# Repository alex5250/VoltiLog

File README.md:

# What it is 
VoltLogV2
This is an small device that allow record an voltage and current in two modes. The simplest mode is when the device is connected to PC and it sends data throught UART over USB. The second mode is when device is connected to power supply and just records data in internal memory. The all software and hardware is open sources and avabile there.
Is Kicad Export of PCB look:

Real PCB look:

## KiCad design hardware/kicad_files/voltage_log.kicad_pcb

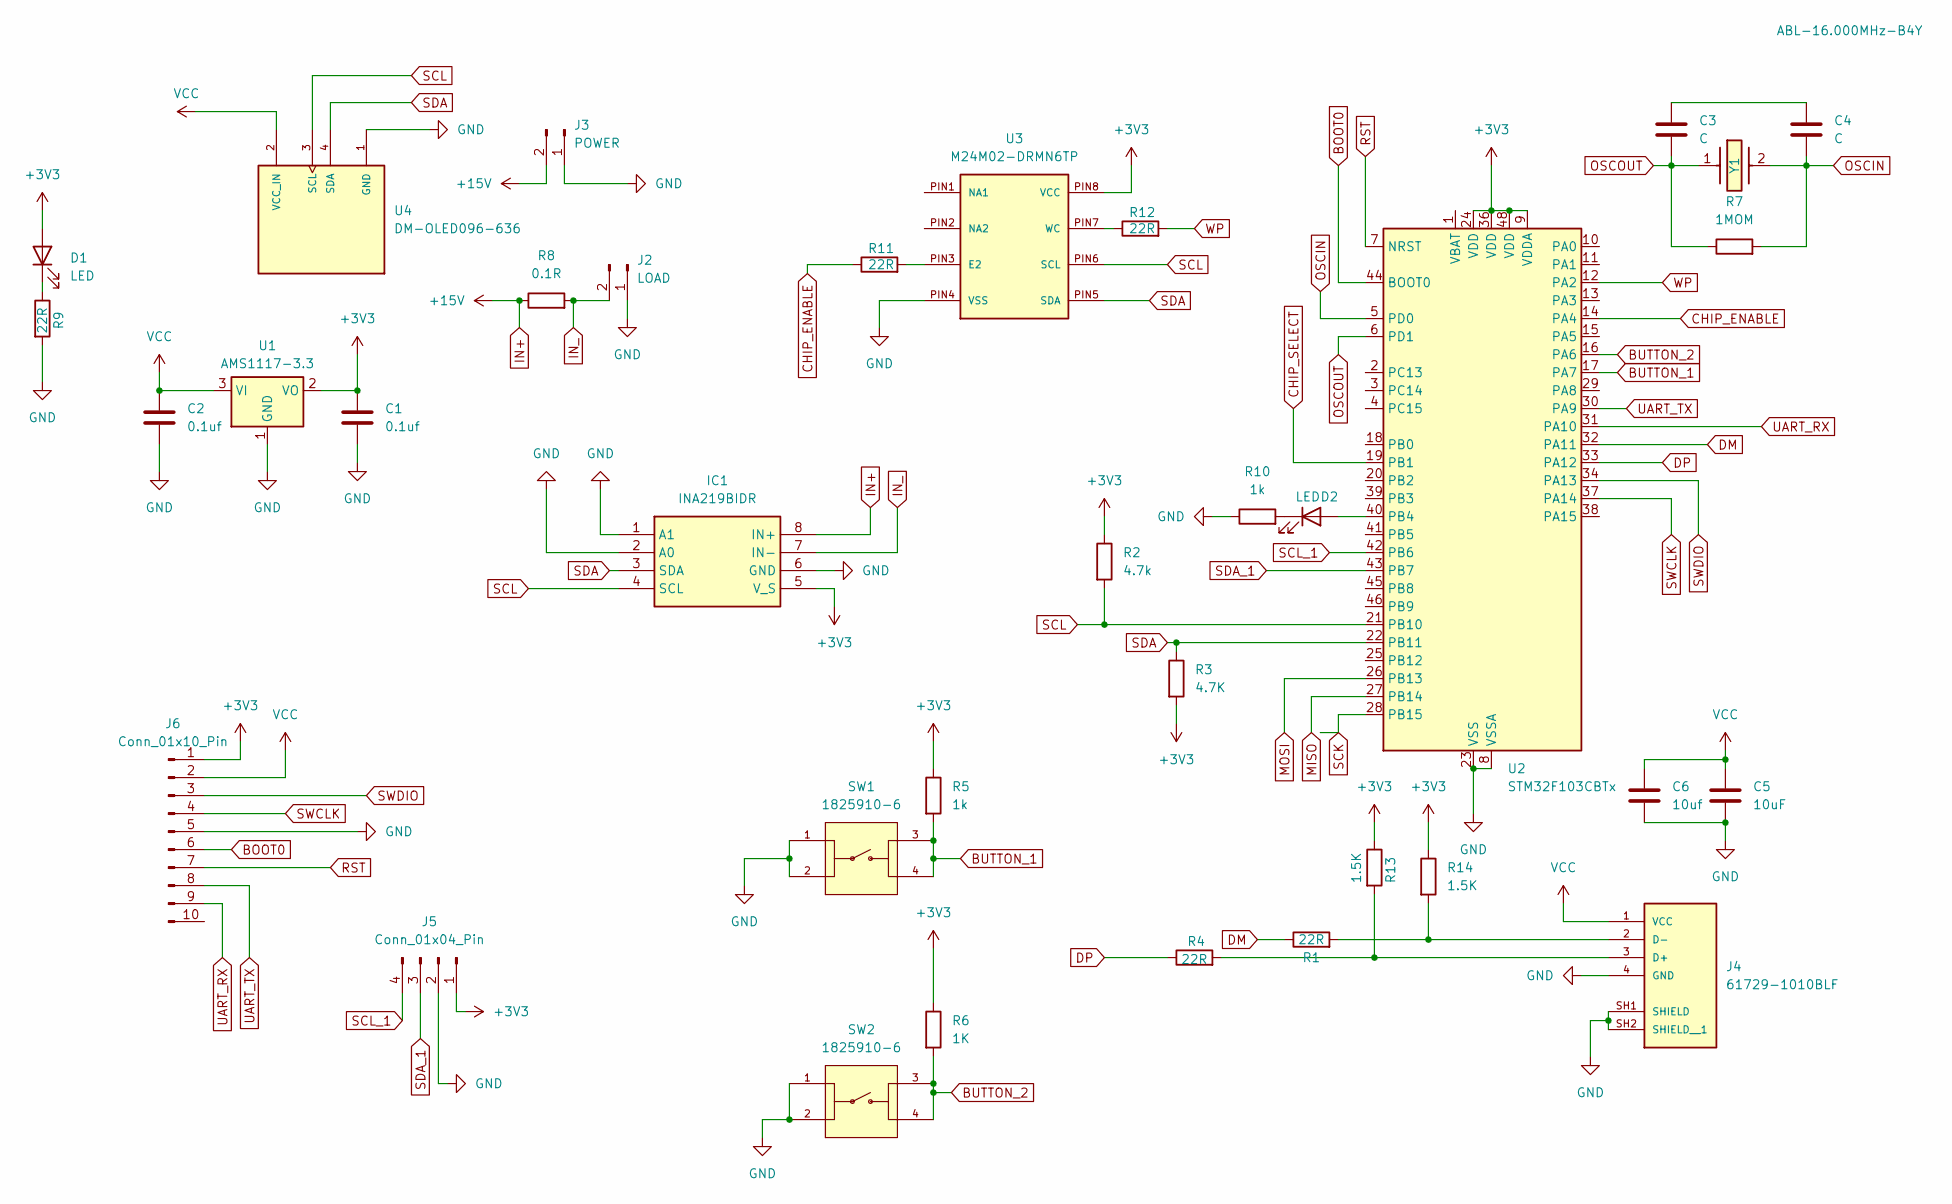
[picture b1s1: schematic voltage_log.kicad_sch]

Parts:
C1, C2: 0.1uf; C_1206_3216Metric
C3, C4: C; C_1206_3216Metric
C5: 10uF; C_1206_3216Metric
C6: 10uf; C_1206_3216Metric
D1, D2: LED; D_1206_3216Metric
IC1: INA219BIDR; SOIC127P600X175-8N; Mouser Part Number 595-INA219BIDR
J2: LOAD; TerminalBlock_Phoenix_MKDS-1,5-2-5.08_1x02_P5.08mm_Horizont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
J3: POWER; TerminalBlock_Phoenix_MKDS-1,5-2-5.08_1x02_P5.08mm_Horizont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
J4: 61729-1010BLF; AMPHENOL_61729-1010BLF; PARTREV AD
J5: Conn_01x04_Pin; JST_XH_S4B-XH-A-1_1x04_P2.50mm_Horizontal
J6: Conn_01x10_Pin; PinHeader_1x10_P2.54mm_Vertical
R1, R4, R9, R11, R12: 22R; R_1206_3216Metric
R2: 4.7k; R_1206_3216Metric
R3: 4.7K; R_1206_3216Metric
R5, R10: 1k; R_1206_3216Metric
R6: 1K; R_1206_3216Metric
R7: 1MOM; R_1206_3216Metric
R8: 0.1R; R_2512_6332Metric
R13, R14: 1.5K; R_1206_3216Metric
SW1, SW2: 1825910-6; SW_1825910-6-4; PARTREV C10
U1: AMS1117-3.3; SOT-223-3_TabPin2
U2: STM32F103CBTx; LQFP-48_7x7mm_P0.5mm
U3: M24M02-DRMN6TP; SOIC8
U4: DM-OLED096-636; MODULE_DM-OLED096-636; PARTREV 2018-09-10
Y1: ABL-16.000MHz-B4Y; ABL; Mouser Part Number 815-ABL-16-B4Y

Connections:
+3V3: C1.1, D1.2 (A), IC1.5 (V_S), J5.1, J6.1, R2.1, R3.2, R5.1, R6.1, R13.1, R14.1, U1.2 (VO), U2.9 (VDDA), U2.24 (VDD), U2.36 (VDD), U2.48 (VDD), U3.PIN8 (VCC)
BOOT0: J6.6, U2.44 (BOOT0)
BUTTON_1: R5.2, SW1.3, SW1.4, U2.17 (PA7)
BUTTON_2: R6.2, SW2.3, SW2.4, U2.16 (PA6)
CHIP_ENABLE: R11.1, U2.14 (PA4)
CHIP_SELECT: U2.19 (PB1)
DM: R1.1, U2.32 (PA11)
DP: R4.1, U2.33 (PA12)
GND: C1.2, C2.2, C5.2, C6.2, IC1.1 (A1), IC1.2 (A0), IC1.6 (GND), J2.1, J3.1, J4.4 (GND), J4.SH1 (SHIELD), J4.SH2 (SHIELD__1), J5.2, J6.5, R9.2, R10.1, SW1.1, SW1.2, SW2.1, SW2.2, U1.1 (GND), U2.8 (VSSA), U2.23 (VSS), U2.35 (VSS), U2.47 (VSS), U3.PIN4 (VSS), U4.1 (GND)
IN+: IC1.8 (IN+), J3.2, R8.1
IN_: IC1.7 (IN-), J2.2, R8.2
MISO: U2.27 (PB14)
MOSI: U2.26 (PB13)
unnamed: C3.1, C4.1
unnamed: D1.1 (K), R9.1
unnamed: D2.2 (A), U2.40 (PB4)
unnamed: D2.1 (K), R10.2
unnamed: J4.3 (D+), R4.2, R13.2
unnamed: J4.2 (D-), R1.2, R14.2
unnamed: R11.2, U3.PIN3 (E2)
unnamed: R12.1, U3.PIN7 (WC)
OSCIN: C4.2, R7.2, U2.5 (PD0), Y1.2
OSCOUT: C3.2, R7.1, U2.6 (PD1), Y1.1
RST: J6.7, U2.7 (NRST)
SCK: U2.28 (PB15)
SCL: IC1.4 (SCL), R2.2, U2.21 (PB10), U3.PIN6 (SCL), U4.3 (SCL)
SCL_1: J5.4, U2.42 (PB6)
SDA: IC1.3 (SDA), R3.1, U2.22 (PB11), U3.PIN5 (SDA), U4.4 (SDA)
SDA_1: J5.3, U2.43 (PB7)
SWCLK: J6.4, U2.37 (PA14)
SWDIO: J6.3, U2.34 (PA13)
UART_RX: J6.9, U2.31 (PA10)
UART_TX: J6.8, U2.30 (PA9)
VCC: C2.1, C5.1, C6.1, J4.1 (VCC), J6.2, U1.3 (VI), U4.2 (VCC_IN)
WP: R12.2, U2.12 (PA2)

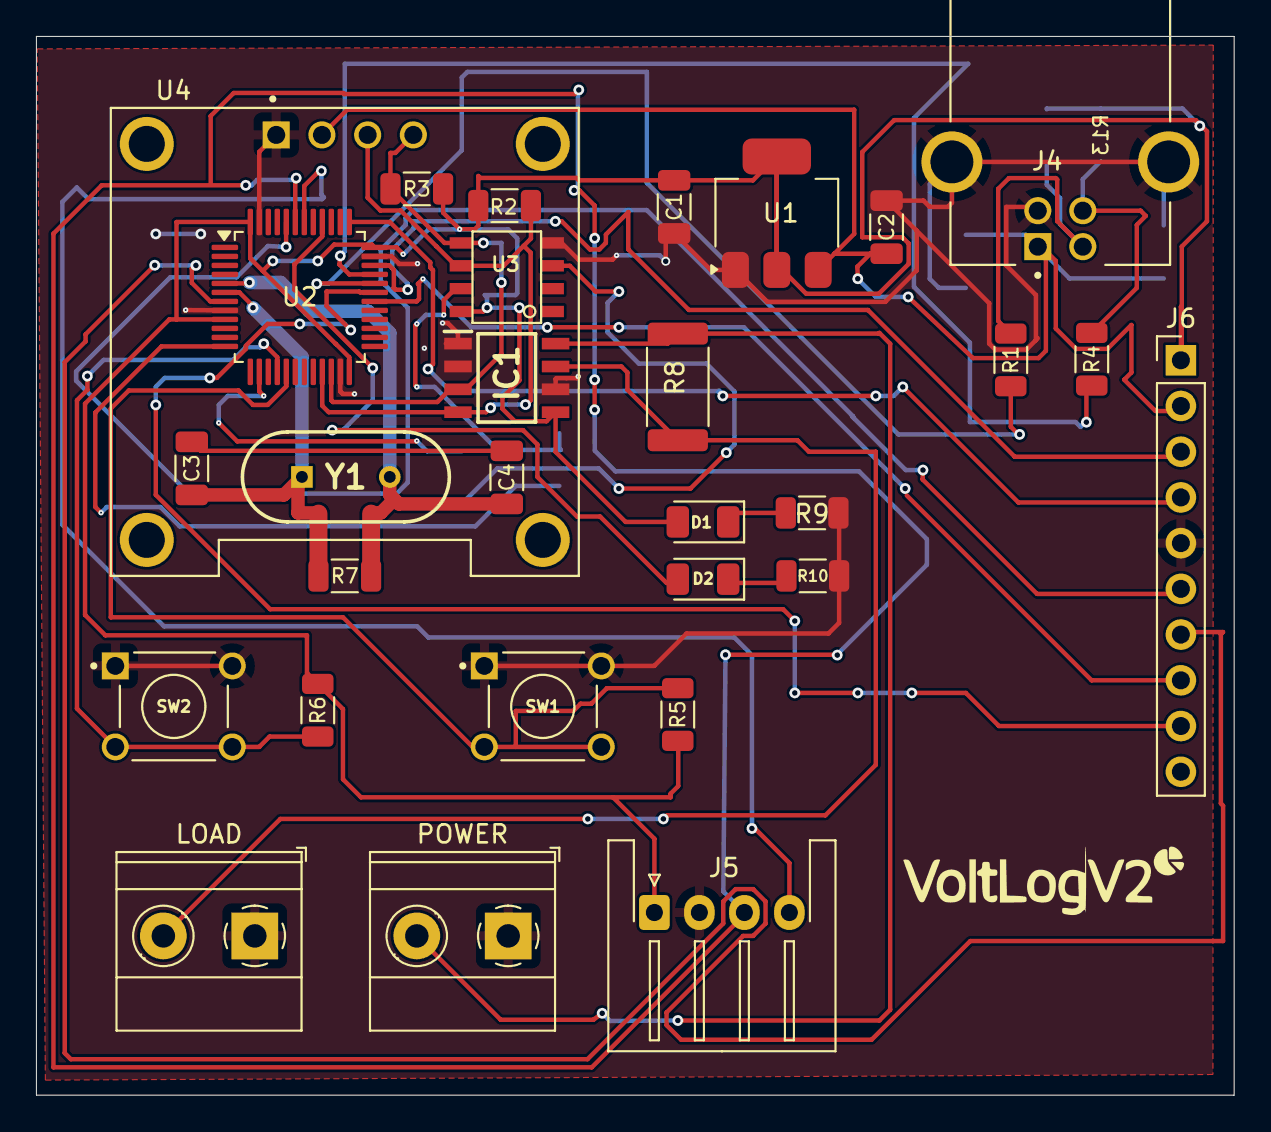
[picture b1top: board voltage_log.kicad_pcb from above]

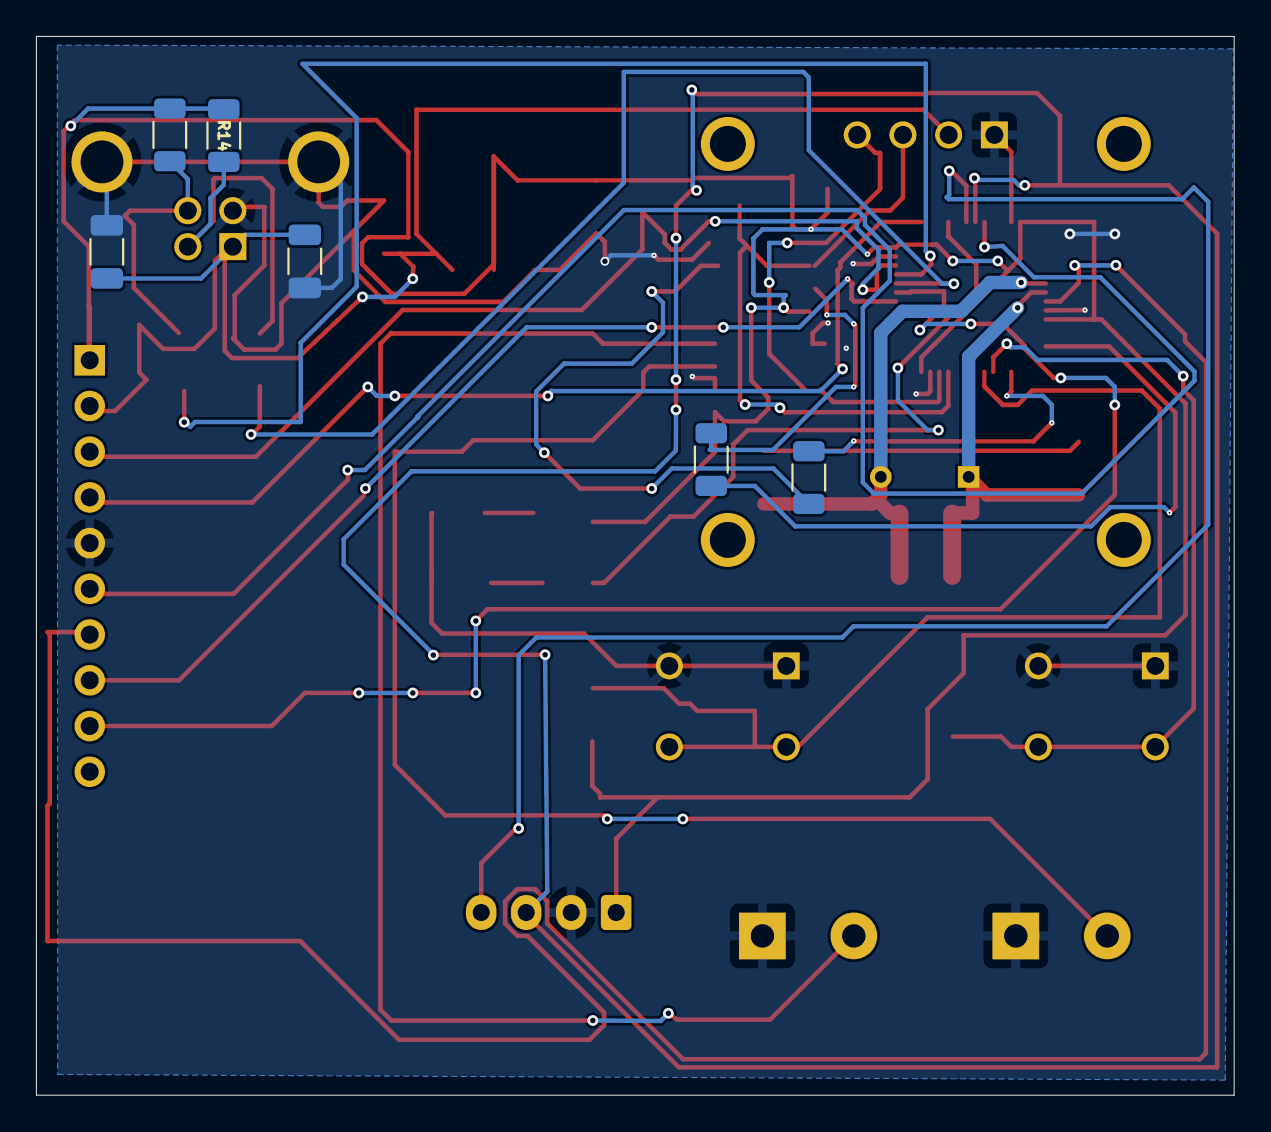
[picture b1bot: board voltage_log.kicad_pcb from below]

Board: 2 copper layers, 66.5 x 58.8 mm, 35 parts (6 on the bottom side), 31 nets.

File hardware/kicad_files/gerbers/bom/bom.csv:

Designator,Footprint,Quantity,Value,LCSC Part #
"C1, C2",1206,2,0.1uf,
"C3, C4",1206,2,C,
"C5, C6",1206,2,10uF,
"D1, D2",1206,2,LED,
IC1,SOIC127P600X175-8N,1,INA219BIDR,
J2,"TerminalBlock_Phoenix_MKDS-1,5-2-5.08_1x02_P5.08mm_Horizontal",1,LOAD,
J3,"TerminalBlock_Phoenix_MKDS-1,5-2-5.08_1x02_P5.08mm_Horizontal",1,POWER,
J4,AMPHENOL_61729-1010BLF,1,61729-1010BLF,
J5,JST_XH_S4B-XH-A-1_1x04_P2.50mm_Horizontal,1,Conn_01x04_Pin,
J6,PinHeader_1x10_P2.54mm_Vertical,1,Conn_01x10_Pin,
"R1, R11, R12, R4, R9",1206,5,22R,
"R10, R5, R6",1206,3,1k,
"R13, R14",1206,2,1.5K,
"R2, R3",1206,2,4.7k,
R7,1206,1,1MOM,
R8,2512,1,0.1R,
"SW1, SW2",SW_1825910-6-4,2,1825910-6,
U1,SOT-223-3_TabPin2,1,AMS1117-3.3,
U2,LQFP-48_7x7mm_P0.5mm,1,STM32F103CBTx,
U3,SOIC8,1,M24M02-DRMN6TP,
U4,MODULE_DM-OLED096-636,1,DM-OLED096-636,
Y1,ABL,1,ABL-16.000MHz-B4Y,

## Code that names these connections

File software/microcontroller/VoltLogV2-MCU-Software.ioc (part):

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Mcu.Name=STM32F103C(8-B)Tx
Mcu.Package=LQFP48
Mcu.UserName=STM32F103CBTx
PA10.Mode=Asynchronous
PA10.Signal=USART1_RX
PA11.Mode=Device
PA11.Signal=USB_DM
PA12.Mode=Device
PA12.Signal=USB_DP
PA13.Mode=Serial_Wire
PA13.Signal=SYS_JTMS-SWDIO
PA14.Mode=Serial_Wire
PA14.Signal=SYS_JTCK-SWCLK
PA2.Signal=GPIO_Output
PA4.Signal=GPIO_Output
PA6.Signal=GPIO_Input
PA7.Signal=GPIO_Input
PA9.Mode=Asynchronous
PA9.Signal=USART1_TX
PB1.Signal=GPIO_Output
PB10.Mode=I2C
PB10.Signal=I2C2_SCL
PB11.Mode=I2C
PB11.Signal=I2C2_SDA
PB4.Signal=GPIO_Output
PB6.Mode=I2C
PB6.Signal=I2C1_SCL
PB7.Mode=I2C
PB7.Signal=I2C1_SDA
PD0-OSC_IN.Mode=HSE-External-Oscillator
PD0-OSC_IN.Signal=RCC_OSC_IN
PD1-OSC_OUT.Mode=HSE-External-Oscillator
PD1-OSC_OUT.Signal=RCC_OSC_OUT
board=custom

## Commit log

2023-01-08 added all files requried
2023-01-08 small bug fixes
2024-08-18 new pcb! all rest comming soon
2024-08-20 rm old version backup
2024-08-20 added message to readme
2024-08-20 added pcb files
2024-08-20 added gerbers zip
2024-08-20 added some images of pcb
2024-08-20 added 3d model and kicad libs used for design
2024-08-20 added kicad libs
2024-08-20 generated project with stm32ide
2024-08-20 fixed cmsis version from v2 to v1
2024-08-20 added stm32-ssd1306 lib for screen
2024-09-17 fixed project and added ui mockups
2024-09-17 NEW PROJECT RECONFIGURED
2024-09-18 added voltlog software
2024-09-18 upload some fixes
2024-09-19 added mn2402 driver
2024-09-19 turned off -fcyclomatic-complexity
